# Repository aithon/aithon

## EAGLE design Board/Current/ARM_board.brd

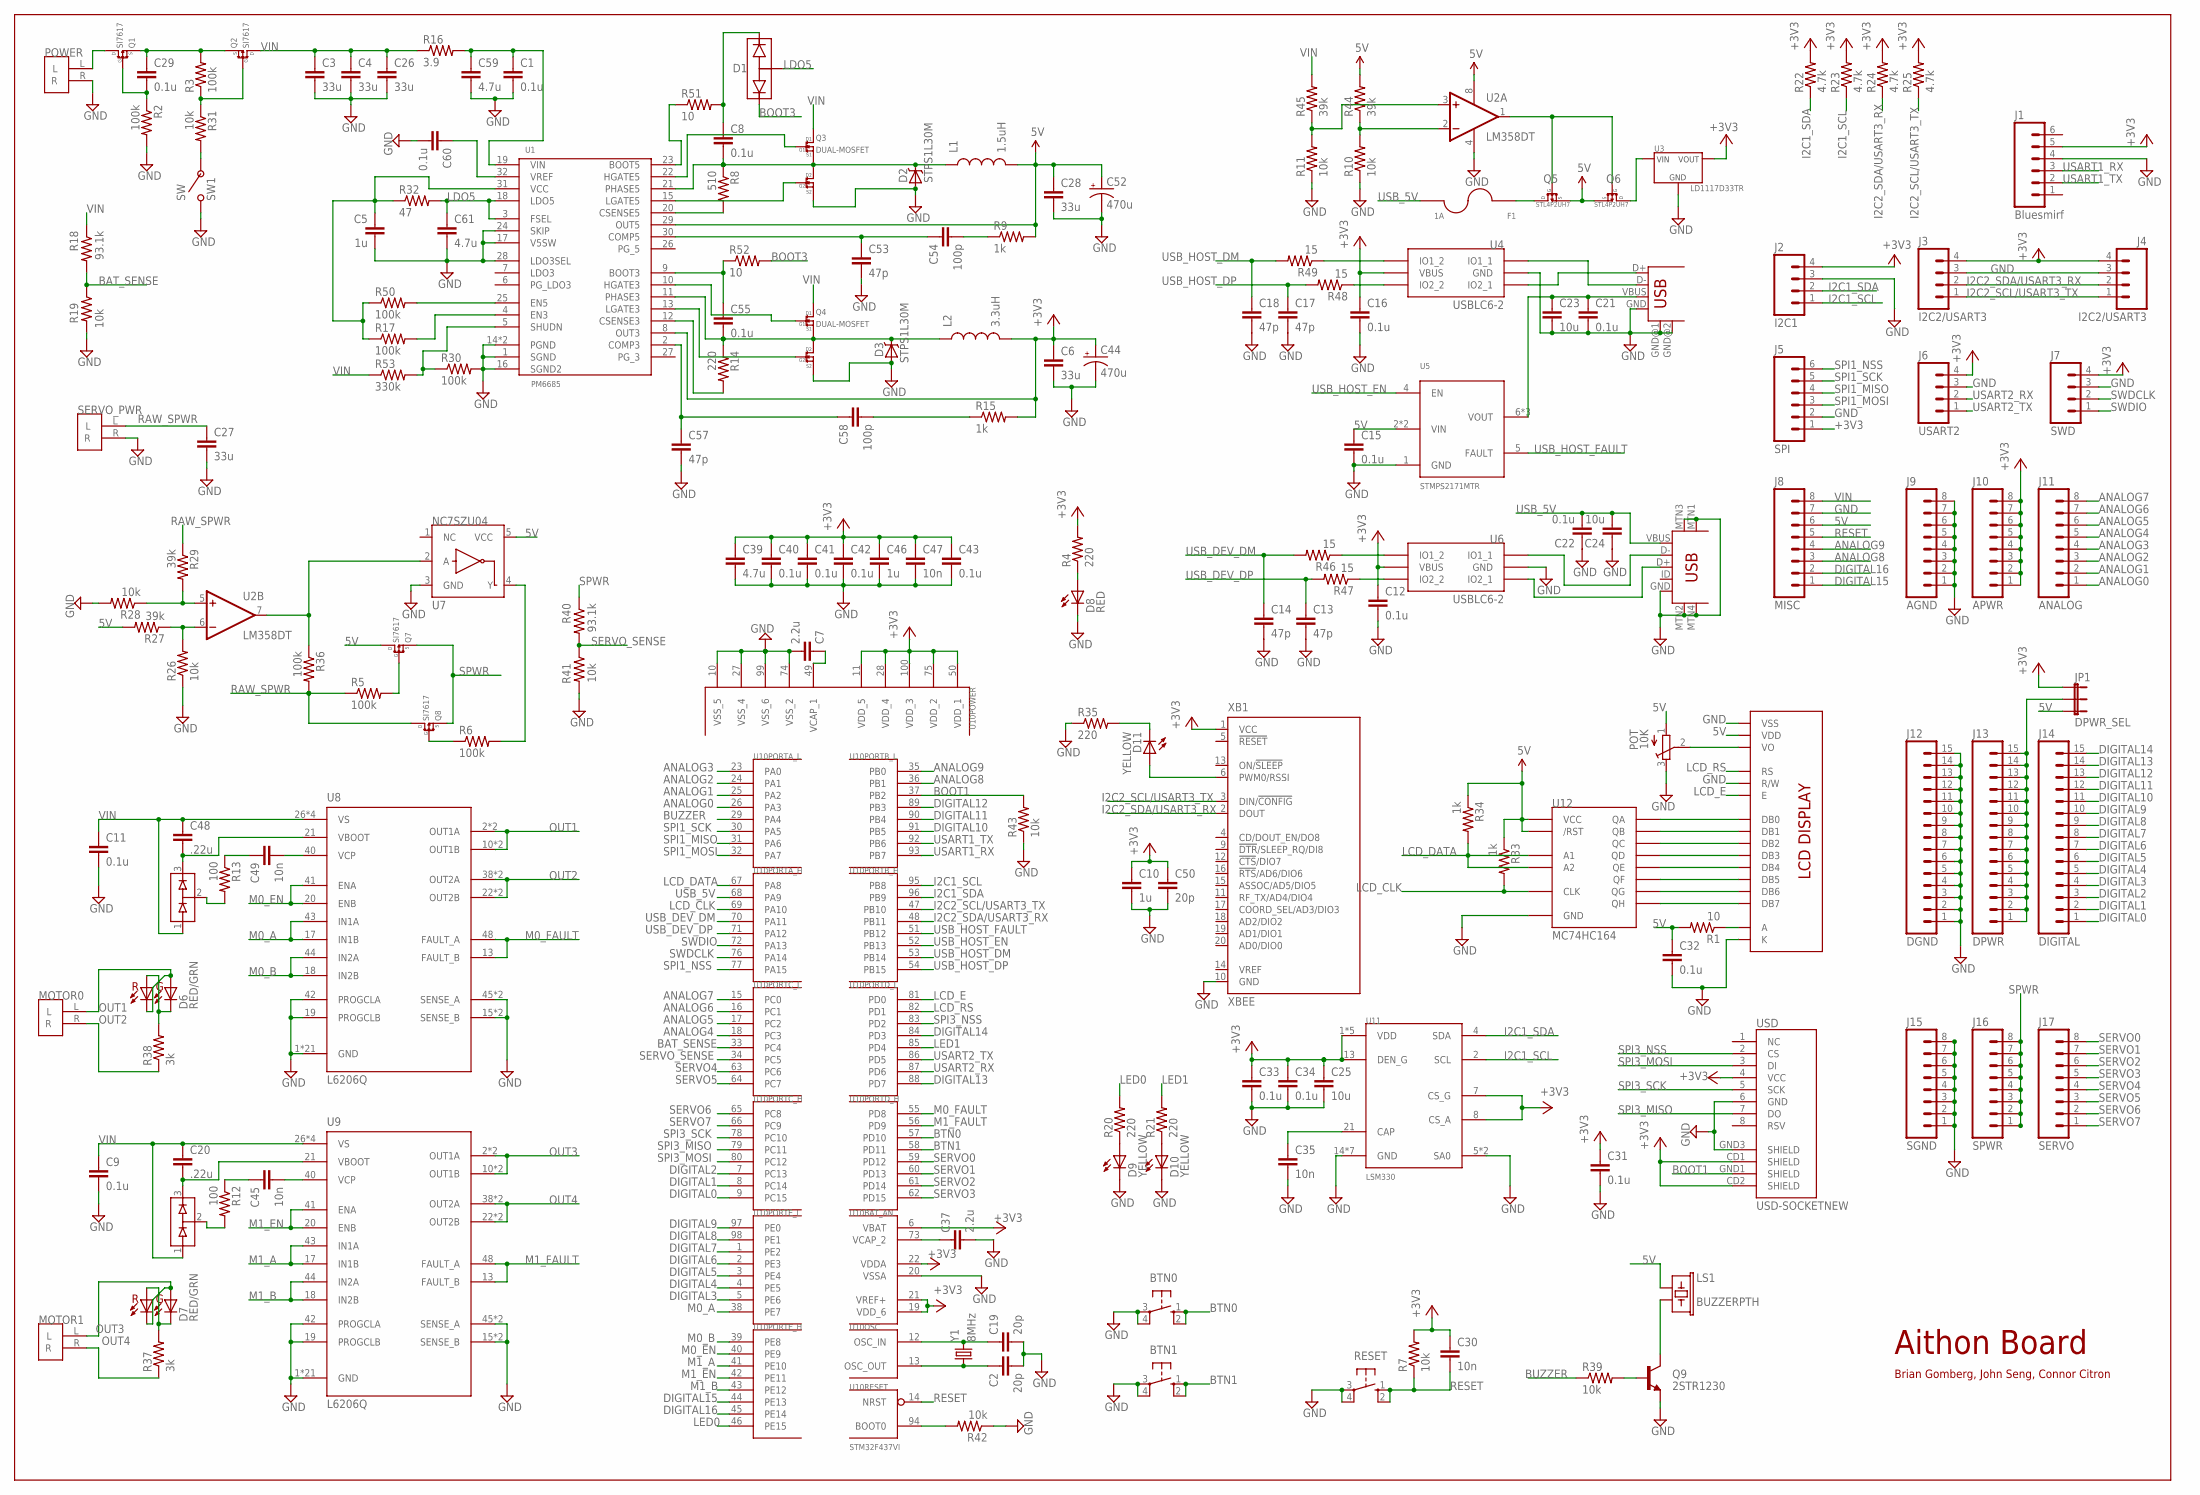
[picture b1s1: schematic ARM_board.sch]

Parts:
BTN0, BTN1: 10-XX; B3F-10XX
C1, C8, C9, C11, C12, C15, C16, C21, C22, C29, C31, C32, C33, C34, C40, C41, C42, C43, C55, C60: 0.1u; 0402-CAP
C2, C19, C50: 20p; 0402-CAP
C3, C4, C26, C27: 33u; 1206
C5, C10, C46: 1u; 0402-CAP
C6, C28: 33u; 0805
C7, C37: 2.2u; 0402-CAP
C13, C14, C17, C18, C53, C57: 47p; 0402-CAP
C20, C48: .22u; 0402-CAP
C23, C24, C25: 10u; 0603-CAP
C30, C35, C45, C47, C49: 10n; 0402-CAP
C39, C59, C61: 4.7u; 0603-CAP
C44, C52: 470u; PANASONIC_D
C54, C58: 100p; 0402-CAP
D1: BAS70-06FILM; SOT-23
D2, D3: STPS1L30M
D4: BAS70-05FILM; SOT-23
D5: BAV99; SOT-23
D6, D7: RED/GRN; LED-0606
D8: RED; CHIP-LED0603
D9, D10, D11: YELLOW; CHIP-LED0603
F1: 1A; 1206
J1: Bluesmirf; 1X06
J2: I2C1; 1X04
J3, J4: I2C2/USART3; 1X04
J5: SPI; 1X06
J6: USART2; 1X04
J7: SWD; 1X04
J8: MISC; 1X08
J9: AGND; 1X08
J10: APWR; 1X08
J11: ANALOG; 1X08
J12: DGND; 1X15
J13: DPWR; 1X15
J14: DIGITAL; 1X15
J15: SGND; 1X08
J16: SPWR; 1X08
J17: SERVO; 1X08
JP1: DPWR_SEL; 1X03
L1: 1.5uH; INDUCTOR-LMIP707
L2: 3.3uH; INDUCTOR-0520CDMCDS
LCD: LCD_DISPLAY; LCD
LS1: BUZZERPTH; BUZZER-12MM
MOTOR0, MOTOR1: 2POS_TERMINAL
POT: 10K; POT
POWER: 2POS_TERMINAL
Q1, Q2, Q7, Q8: SI7617; POWERPAK1212-8
Q3, Q4: DUAL-MOSFET; DUAL-MOSFET-STL60N32N3LL
Q5, Q6: STL4P2UH7; POWERFLAT
Q9: 2STR1230; SOT23-3
R1, R51, R52: 10; 0402-RES
R2, R3, R5, R6, R17, R30, R36, R50: 100k; 0402-RES
R4, R14, R20, R21, R35: 220; 0402-RES
R7, R10, R11, R19, R26, R28, R31, R39, R41, R42, R43: 10k; 0402-RES
R8: 510; 0402-RES
R9, R15, R33, R34: 1k; 0402-RES
R12, R13: 100; 0402-RES
R16: 3.9; 0402-RES
R18, R40: 93.1k; 0402-RES
R22, R23, R24, R25: 4.7k; 0402-RES
R27, R29, R44, R45: 39k; 0402-RES
R32: 47; 0402-RES
R37, R38: 3k; 0603-RES
R46, R47, R48, R49: 15; 0402-RES
R53: 330k; 0402-RES
RESET: 10-XX; B3F-10XX
SERVO_PWR: 2POS_TERMINAL
SW1: SW
U1: PM6685; VFQFPN-32
U2: LM358DT; SO08
U3: LD1117D33TR; 8-SOIC
U4, U6: USBLC6-2; SOT23-6L
U5: STMPS2171MTR; 8-SOIC
U7: NC7SZU04; SC70
U8, U9: L6206Q; VFQFPN48
U10: STM32F437VI; TQFP100
U11: LSM330
U12: MC74HC164; TSSOP-14
USB1: USB-A-S
USB2: USB-MINIB-5PIN; USB-MINIB
USD: USD-SOCKETNEW; MICRO-SD-SOCKET-PP
XB1: XBEE; MPN XBP24-Z7UIT-004
Y1: 8MHz; HC49UP

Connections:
5V: C15.1, C28.1, C32.1, C52.+, J8.6, JP1.3, L1.P$2 (2), LCD.VDD, LS1.+ (1), POT.1 (A), Q5.4 (S), Q5.7 (S), Q6.4 (S), Q6.7 (S), Q7.5 (D), Q7.6 (D), Q7.7 (D), Q7.8 (D), Q7.PAD (D), R1.2, R9.2, R27.2, R33.1, R34.1, R44.2, U1.29 (OUT5), U2.8 (V+), U5.2 (VIN), U5.3 (VIN), U7.5 (VCC), U12.9 (/RST), U12.14 (VCC)
+3V3: C6.1, C10.1, C12.1, C16.1, C25.1, C30.1, C31.1, C33.1, C34.1, C39.1, C40.1, C41.1, C42.1, C43.1, C44.+, C46.1, C47.1, C50.1, J1.5, J2.4, J3.4, J4.4, J5.1, J6.4, J7.4, J10.1, J10.2, J10.3, J10.4, J10.5, J10.6, J10.7, J10.8, JP1.1, L2.P$2 (2), R4.2, R7.2, R15.2, R22.2, R23.2, R24.2, R25.2, U1.8 (OUT3), U3.2 (VOUT), U3.3 (VOUT), U3.6 (VOUT), U3.7 (VOUT), U4.P$5 (VBUS), U6.P$5 (VBUS), U10.6 (VBAT), U10.11 (VDD_5), U10.19 (VDD_6), U10.21 (VREF+), U10.22 (VDDA), U10.28 (VDD_4), U10.50 (VDD_1), U10.75 (VDD_2), U10.100 (VDD_3), U11.1 (VDD), U11.3 (VDD), U11.7 (CS_G), U11.8 (CS_A), U11.13 (DEN_G), U11.22 (VDD), U11.23 (VDD), U11.24 (VDD), USD.4 (VCC), USD.CD1 (SHIELD), USD.CD2 (SHIELD), XB1.1 (VCC)
ANALOG0: J11.1, U10.26 (PA3)
ANALOG1: J11.2, U10.25 (PA2)
ANALOG2: J11.3, U10.24 (PA1)
ANALOG3: J11.4, U10.23 (PA0)
ANALOG4: J11.5, U10.18 (PC3)
ANALOG5: J11.6, U10.17 (PC2)
ANALOG6: J11.7, U10.16 (PC1)
ANALOG7: J11.8, U10.15 (PC0)
ANALOG8: J8.3, U10.36 (PB1)
ANALOG9: J8.4, U10.35 (PB0)
BAT_SENSE: R18.2, R19.1, U10.33 (PC4)
BOOT1: R43.2, U10.37 (PB2), USD.GND1 (SHIELD)
BOOT3: D1.P$2, R52.2
BTN0: BTN0.1 (S), BTN0.2 (S1), U10.57 (PD10)
BTN1: BTN1.1 (S), BTN1.2 (S1), U10.58 (PD11)
BUZZER: R39.1, U10.29 (PA4)
DIGITAL0: J14.1, U10.9 (PC15)
DIGITAL1: J14.2, U10.8 (PC14)
DIGITAL2: J14.3, U10.7 (PC13)
DIGITAL3: J14.4, U10.5 (PE6)
DIGITAL4: J14.5, U10.4 (PE5)
DIGITAL5: J14.6, U10.3 (PE4)
DIGITAL6: J14.7, U10.2 (PE3)
DIGITAL7: J14.8, U10.1 (PE2)
DIGITAL8: J14.9, U10.98 (PE1)
DIGITAL9: J14.10, U10.97 (PE0)
DIGITAL10: J14.11, U10.91 (PB5)
DIGITAL11: J14.12, U10.90 (PB4)
DIGITAL12: J14.13, U10.89 (PB3)
DIGITAL13: J14.14, U10.88 (PD7)
DIGITAL14: J14.15, U10.84 (PD3)
DIGITAL15: J8.1, U10.44 (PE13)
DIGITAL16: J8.2, U10.45 (PE14)
GND: BTN0.3, BTN0.4 (P1), BTN1.3, BTN1.4 (P1), C1.2, C2.2, C3.2, C4.2, C5.2, C6.2, C7.2, C9.2, C10.2, C11.2, C12.2, C13.2, C14.2, C15.2, C16.2, C17.2, C18.2, C19.2, C21.2, C22.1, C23.2, C24.1, C25.2, C26.2, C27.2, C28.2, C31.2, C32.2, C33.2, C34.2, C35.2, C37.2, C39.2, C40.2, C41.2, C42.2, C43.2, C44.-, C46.2, C47.2, C50.2, C52.-, C53.2, C57.2, C59.2, C60.2, C61.2, D2.P$1 (A), D3.P$1 (A), D8.C, D9.C, D10.C, J1.4, J2.3, J3.3, J4.3, J5.2, J6.3, J7.3, J8.7, J9.1, J9.2, J9.3, J9.4, J9.5, J9.6, J9.7, J9.8, J12.1, J12.2, J12.3, J12.4, J12.5, J12.6, J12.7, J12.8, J12.9, J12.10, J12.11, J12.12, J12.13, J12.14, J12.15, J15.1, J15.2, J15.3, J15.4, J15.5, J15.6, J15.7, J15.8, LCD.K, LCD.R/W, LCD.VSS, POT.3 (E), POWER.R, Q3.5/6/7 (S2), Q4.5/6/7 (S2), Q9.2 (E), R2.2, R10.1, R11.1, R19.2, R26.1, R28.2, R30.2, R35.1, R41.2, R42.1, R43.1, RESET.3, RESET.4 (P1), SERVO_PWR.R, SW1.P$1, SW1.P$3, U1.1 (SGND), U1.14 (PGND), U1.16 (SGND2), U1.17 (V5SW), U1.24 (SKIP), U1.28 (LDO3SEL), U1.PAD (PGND), U2.4 (V-), U3.1 (GND), U4.P$2 (GND), U5.1 (GND), U6.P$2 (GND), U7.3 (GND), U8.1 (GND), U8.4 (GND), U8.5 (GND), U8.6 (GND), U8.7 (GND), U8.8 (GND), U8.9 (GND), U8.12 (GND), U8.14 (GND), U8.15 (SENSE_B), U8.16 (SENSE_B)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
I2C1_SCL: J2.1, R23.1, U10.95 (PB8), U11.2 (SCL)
I2C1_SDA: J2.2, R22.1, U10.96 (PB9), U11.4 (SDA)
I2C2_SCL/USART3_TX: J3.1, J4.1, R25.1, U10.47 (PB10), XB1.3 (DIN/!CONFIG)
I2C2_SDA/USART3_RX: J3.2, J4.2, R24.1, U10.48 (PB11), XB1.2 (DOUT)
LCD_CLK: R33.2, U10.69 (PA10), U12.8 (CLK)
LCD_DATA: R34.2, U10.67 (PA8), U12.1 (A1), U12.2 (A2)
LCD_E: LCD.E, U10.81 (PD0)
LCD_RS: LCD.RS, U10.82 (PD1)
LDO5: C61.1, D1.P$0, R32.2, U1.3 (FSEL), U1.18 (LDO5)
LED0: R20.2, U10.46 (PE15)
LED1: R21.2, U10.85 (PD4)
M0_A: U8.17 (IN1B), U8.43 (IN1A), U10.38 (PE7)
M0_B: U8.18 (IN2B), U8.44 (IN2A), U10.39 (PE8)
M0_EN: U8.20 (ENB), U8.41 (ENA), U10.40 (PE9)
M0_FAULT: U8.13 (FAULT_B), U8.48 (FAULT_A), U10.55 (PD8)
M1_A: U9.17 (IN1B), U9.43 (IN1A), U10.41 (PE10)
M1_B: U9.18 (IN2B), U9.44 (IN2A), U10.43 (PE12)
M1_EN: U9.20 (ENB), U9.41 (ENA), U10.42 (PE11)
M1_FAULT: U9.13 (FAULT_B), U9.48 (FAULT_A), U10.56 (PD9)
unnamed: POWER.L, Q1.5 (D), Q1.6 (D), Q1.7 (D), Q1.8 (D), Q1.PAD (D)
unnamed: C29.2, Q1.4 (G), R2.1
unnamed: R42.2, U10.94 (BOOT0)
unnamed: C37.1, U10.73 (VCAP_2)
unnamed: R11.2, R45.1, U2.3 (+IN)
unnamed: R46.1, U6.P$6 (IO1_2)
unnamed: C60.1, U1.32 (VREF)
unnamed: U6.P$3 (IO2_1), USB2.D+
unnamed: D8.A, R4.1
unnamed: R31.2, SW1.P$2
unnamed: C35.1, U11.21 (CAP)
unnamed: R28.1, R29.2, U2.5 (+IN)
unnamed: U4.P$3 (IO2_1), USB1.D+
unnamed: Q5.3 (G), Q6.3 (G), U2.1 (OUT)
unnamed: C5.1, R17.1, R32.1, R50.1, U1.31 (VCC)
unnamed: U4.P$1 (IO1_1), USB1.D-
unnamed: U6.P$1 (IO1_1), USB2.D-
unnamed: D11.C, R35.2
unnamed: J13.1, J13.2, J13.3, J13.4, J13.5, J13.6, J13.7, J13.8, J13.9, J13.10, J13.11, J13.12, J13.13, J13.14, J13.15, JP1.2
unnamed: R51.1, U1.23 (BOOT5)
unnamed: C21.1, C23.1, U5.6 (VOUT), U5.7 (VOUT), U5.8 (VOUT), USB1.VBUS
unnamed: Q6.1 (D), Q6.2 (D), Q6.5 (D), Q6.6 (D), Q6.8 (D), U3.4 (VIN)
unnamed: C29.1, Q1.1 (S), Q1.2 (S), Q1.3 (S), Q2.1 (S), Q2.2 (S), Q2.3 (S), R3.2
unnamed: C7.1, U10.49 (VCAP_1)
unnamed: C8.1, D1.P$1, R51.2
unnamed: R26.2, R27.1, U2.6 (-IN)
unnamed: R36.1, U2.7 (OUT), U7.2 (A)
unnamed: LS1.- (2), Q9.3 (C)
unnamed: D11.A, XB1.6 (PWM0/RSSI)
unnamed: R6.2, U7.4 (Y)
unnamed: LCD.VO, POT.2 (S)
unnamed: F1.1, Q5.1 (D), Q5.2 (D), Q5.5 (D), Q5.6 (D), Q5.8 (D)
unnamed: R47.1, U6.P$4 (IO2_2)
unnamed: R48.1, U4.P$4 (IO2_2)
unnamed: R10.2, R44.1, U2.2 (-IN)
unnamed: R49.1, U4.P$6 (IO1_2)
unnamed: C45.1, R12.1
unnamed: C45.2, U9.40 (VCP)
unnamed: C20.2, D5.3, U9.21 (VBOOT)
unnamed: D5.2, R12.2
unnamed: C49.1, R13.1
unnamed: D9.A, R20.1
unnamed: D10.A, R21.1
unnamed: Q4.8 (G2), U1.13 (LGATE3)
unnamed: C49.2, U8.40 (VCP)
unnamed: C19.1, U10.12 (OSC_IN), Y1.2
unnamed: C2.1, U10.13 (OSC_OUT), Y1.1
unnamed: C48.2, D4.3, U8.21 (VBOOT)
unnamed: D4.2, R13.2
unnamed: Q7.4 (G), R5.2
unnamed: D7.1, D7.4, R37.2
unnamed: D6.1, D6.4, R38.2
unnamed: Q8.4 (G), R6.1
unnamed: LCD.A, R1.1
unnamed: R8.2, U1.20 (CSENSE5)
unnamed: Q3.1 (G1), U1.22 (HGATE5)
unnamed: Q3.8 (G2), U1.15 (LGATE5)
unnamed: LCD.DB0, U12.3 (QA)
unnamed: C55.1, R52.1, U1.9 (BOOT3)
unnamed: LCD.DB1, U12.4 (QB)
unnamed: LCD.DB2, U12.5 (QC)
unnamed: LCD.DB3, U12.6 (QD)
unnamed: LCD.DB4, U12.10 (QE)
unnamed: LCD.DB5, U12.11 (QF)
unnamed: Q9.1 (B), R39.2
unnamed: C8.2, D2.C2 (C), D2.P$2 (C), L1.P$1 (1), Q3.S1D2 (S1), R8.1, U1.21 (PHASE5)
unnamed: C54.2, R9.1
unnamed: Q2.4 (G), R3.1, R31.1
unnamed: C53.1, C54.1, U1.30 (COMP5)
unnamed: LCD.DB6, U12.12 (QG)
unnamed: LCD.DB7, U12.13 (QH)
unnamed: Q4.1 (G1), U1.10 (HGATE3)
unnamed: C55.2, D3.C2 (C), D3.P$2 (C), L2.P$1 (1), Q4.S1D2 (S1), R14.1, U1.11 (PHASE3)
unnamed: R14.2, U1.12 (CSENSE3)
unnamed: C57.1, C58.1, U1.2 (COMP3)
unnamed: C58.2, R15.1
unnamed: C1.1, C59.1, R16.2, U1.19 (VIN)
unnamed: R30.1, R53.2, U1.5 (SHUDN)
unnamed: R17.2, U1.4 (EN3)
unnamed: R50.2, U1.25 (EN5)
OUT1: D6.2, D6.3, MOTOR0.L, U8.2 (OUT1A), U8.3 (OUT1A), U8.10 (OUT1B), U8.11 (OUT1B)
OUT2: MOTOR0.R, R38.1, U8.22 (OUT2B), U8.23 (OUT2B), U8.38 (OUT2A), U8.39 (OUT2A)
OUT3: D7.2, D7.3, MOTOR1.L, U9.2 (OUT1A), U9.3 (OUT1A), U9.10 (OUT1B), U9.11 (OUT1B)
OUT4: MOTOR1.R, R37.1, U9.22 (OUT2B), U9.23 (OUT2B), U9.38 (OUT2A), U9.39 (OUT2A)
RAW_SPWR: C27.1, Q8.5 (D), Q8.6 (D), Q8.7 (D), Q8.8 (D), Q8.PAD (D), R5.1, R29.1, R36.2, SERVO_PWR.L
RESET: C30.2, J8.5, R7.1, RESET.1 (S), RESET.2 (S1), U10.14 (NRST)
SERVO0: J17.8, U10.59 (PD12)
SERVO1: J17.7, U10.60 (PD13)
SERVO2: J17.6, U10.61 (PD14)
SERVO3: J17.5, U10.62 (PD15)
SERVO4: J17.4, U10.63 (PC6)
SERVO5: J17.3, U10.64 (PC7)
SERVO6: J17.2, U10.65 (PC8)
SERVO7: J17.1, U10.66 (PC9)
SERVO_SENSE: R40.2, R41.1, U10.34 (PC5)
SPI1_MISO: J5.4, U10.31 (PA6)
SPI1_MOSI: J5.3, U10.32 (PA7)
SPI1_NSS: J5.6, U10.77 (PA15)
SPI1_SCK: J5.5, U10.30 (PA5)
SPI3_MISO: U10.79 (PC11), USD.7 (DO)
SPI3_MOSI: U10.80 (PC12), USD.3 (DI)
SPI3_NSS: U10.83 (PD2), USD.2 (CS)
SPI3_SCK: U10.78 (PC10), USD.5 (SCK)
SPWR: J16.1, J16.2, J16.3, J16.4, J16.5, J16.6, J16.7, J16.8, Q7.1 (S), Q7.2 (S), Q7.3 (S), Q8.1 (S), Q8.2 (S), Q8.3 (S), R40.1
SWDCLK: J7.2, U10.76 (PA14)
SWDIO: J7.1, U10.72 (PA13)
USART1_RX: J1.3, U10.93 (PB7)
USART1_TX: J1.2, U10.92 (PB6)
USART2_RX: J6.2, U10.87 (PD6)
USART2_TX: J6.1, U10.86 (PD5)
USB_5V: C22.2, C24.2, F1.2, U10.68 (PA9), USB2.VBUS
USB_DEV_DM: C14.1, R46.2, U10.70 (PA11)
USB_DEV_DP: C13.1, R47.2, U10.71 (PA12)
USB_HOST_DM: C18.1, R49.2, U10.53 (PB14)
USB_HOST_DP: C17.1, R48.2, U10.54 (PB15)
USB_HOST_EN: U5.4 (EN), U10.52 (PB13)
USB_HOST_FAULT: U5.5 (FAULT), U10.51 (PB12)
VIN: C3.1, C4.1, C9.1, C11.1, C20.1, C26.1, C48.1, D4.1, D5.1, J8.8, Q2.5 (D), Q2.6 (D), Q2.7 (D), Q2.8 (D), Q2.PAD (D), Q3.2/3/4 (D1), Q3.D1, Q4.2/3/4 (D1), Q4.D1, R16.1, R18.1, R45.2, R53.1, U8.26 (VS), U8.27 (VS), U8.34 (VS), U8.35 (VS), U9.26 (VS), U9.27 (VS), U9.34 (VS), U9.35 (VS)

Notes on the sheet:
Aithon Board
Brian Gomberg, John Seng, Connor Citron

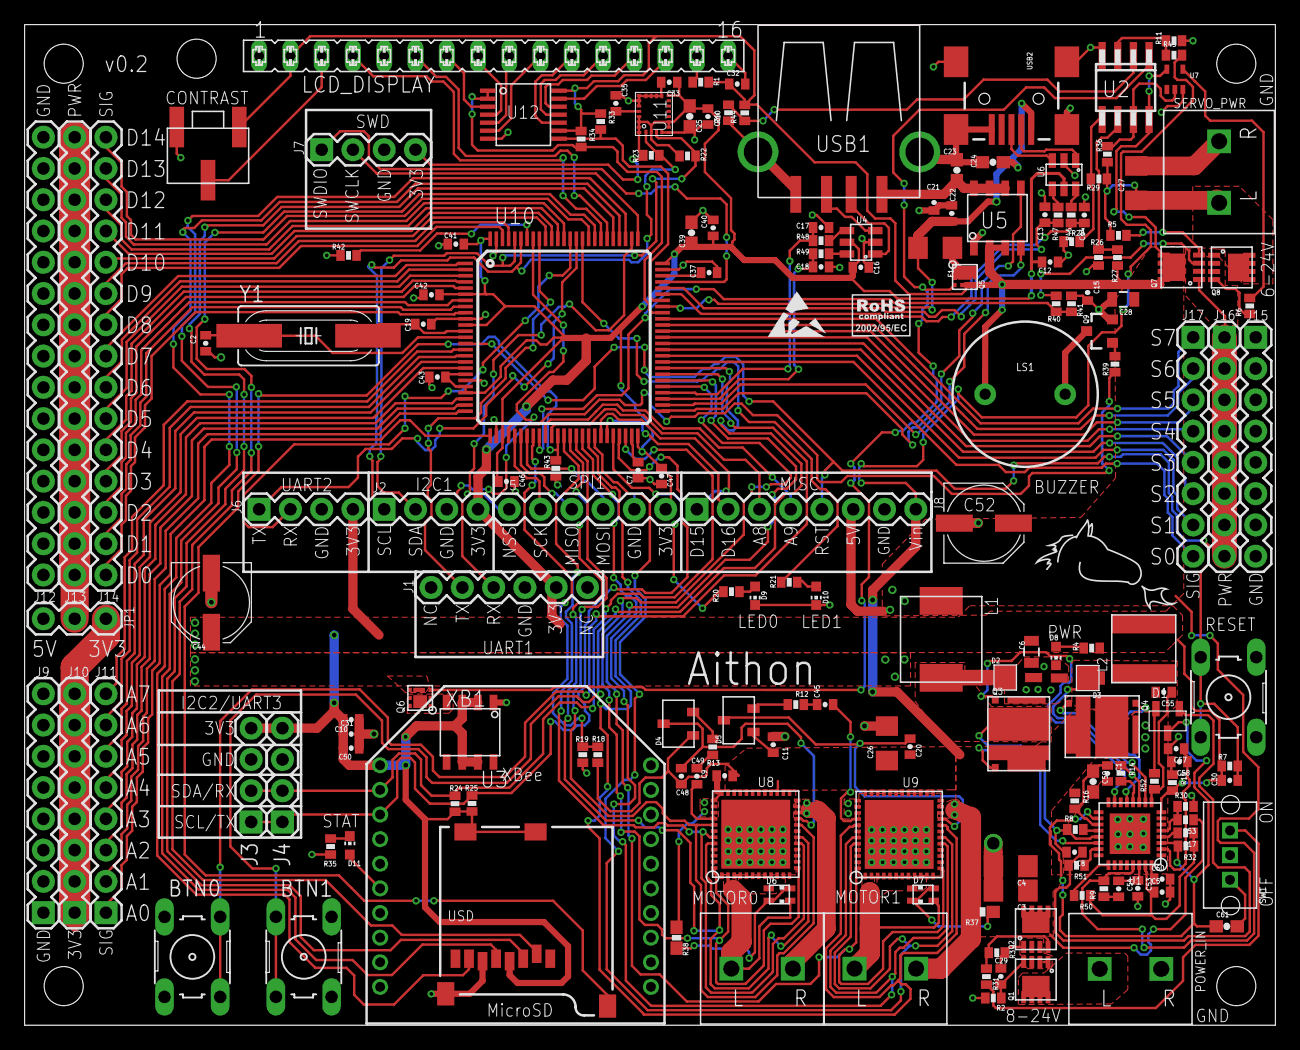
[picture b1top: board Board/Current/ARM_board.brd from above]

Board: 2 copper layers, 101.6 x 81.3 mm, 179 parts (0 on the bottom side), 173 nets.

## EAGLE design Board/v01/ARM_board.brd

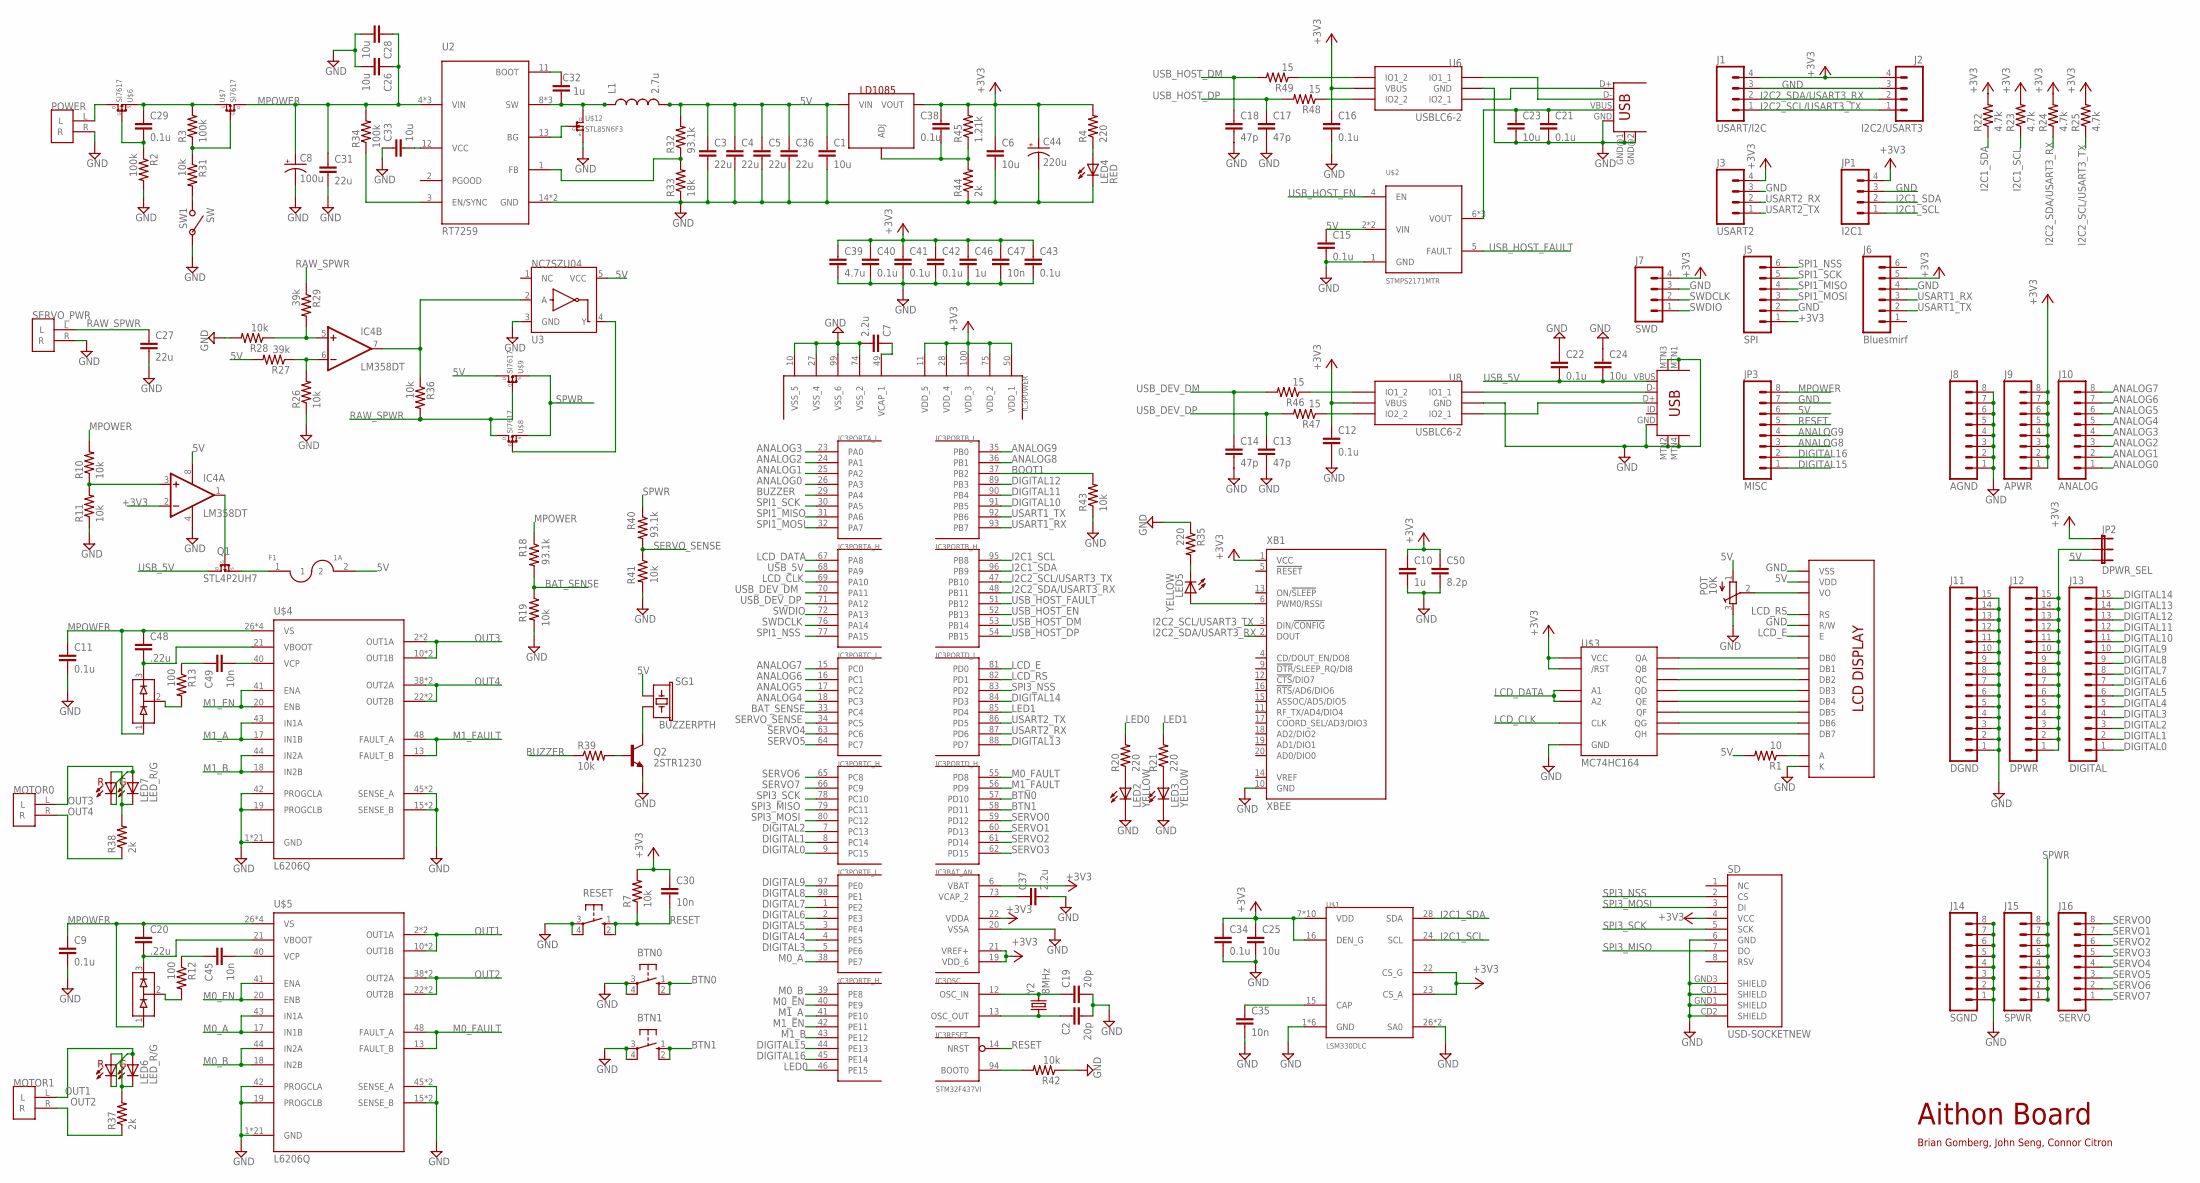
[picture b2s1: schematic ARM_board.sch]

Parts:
BTN0, BTN1: 10-XX; B3F-10XX
C1, C6, C25, C33: 10u; 0603-CAP
C2, C19: 20p; 0402-CAP
C3, C4, C5, C36: 22u; 0805
C7, C37: 2.2u; 0402-CAP
C8: 100u; PANASONIC_D
C9: 0.1u; 0603-CAP
C10, C32: 1u; 0603-CAP
C11: 0.1u; 0805
C12, C15, C16, C21, C22, C29, C34, C38, C40, C41, C42, C43: 0.1u; 0402-CAP
C13, C14, C17, C18: 47p; 0402-CAP
C20, C48: .22u; 0402-CAP
C23, C24, C26, C28: 10u; 0805
C27, C31: 22u; 1206
C30, C35, C45, C47, C49: 10n; 0402-CAP
C39: 4.7u; 0603-CAP
C44: 220u; PANASONIC_D
C46: 1u; 0402-CAP
C50: 8.2p; 0402-CAP
F1: 1A; 1206
IC3: STM32F437VI; TQFP100
IC4: LM358DT; SO08
J1: USART/I2C; 1X04
J2: I2C2/USART3; 1X04
J3: USART2; 1X04
J5: SPI; 1X06
J6: Bluesmirf; 1X06
J7: SWD; 1X04
J8: AGND; 1X08
J9: APWR; 1X08
J10: ANALOG; 1X08
J11: DGND; 1X15
J12: DPWR; 1X15
J13: DIGITAL; 1X15
J14: SGND; 1X08
J15: SPWR; 1X08
J16: SERVO; 1X08
JP1: I2C1; 1X04
JP2: DPWR_SEL; 1X03
JP3: MISC; 1X08
L1: 2.7u; INDUCTOR
LCD: LCD_DISPLAY; LCD
LD1085: AP1084; DPAK
LED2, LED3, LED5: YELLOW; CHIP-LED0603
LED4: RED; CHIP-LED0603
LED6, LED7: LED_R/G; LED-0606
MOTOR0, MOTOR1: 2POS_TERMINAL
POT: 10K; POT
POWER: 2POS_TERMINAL
Q1: STL4P2UH7; POWERFLAT
Q2: 2STR1230; SOT23-3
R1: 10; 0402-RES
R2, R3, R34: 100k; 0402-RES
R4, R20, R21, R35: 220; 0402-RES
R7, R10, R11, R19, R26, R28, R31, R36, R39, R41, R42, R43: 10k; 0402-RES
R12, R13: 100; 0402-RES
R18, R32, R40: 93.1k; 0402-RES
R22, R23, R24, R25: 4.7k; 0402-RES
R27, R29: 39k; 0402-RES
R33: 18k; 0402-RES
R37, R38, R44: 2k; 0402-RES
R45: 1.21k; 0402-RES
R46, R47, R48, R49: 15; 0402-RES
RESET: 10-XX; B3F-10XX
SD: USD-SOCKETNEW; MICRO-SD-SOCKET-PP
SERVO_PWR: 2POS_TERMINAL
SG1: BUZZERPTH; BUZZER-12MM
SW1: SW
U2: RT7259; WDFN-14L
U3: NC7SZU04; SC70
U6, U8: USBLC6-2; SOT23-6L
U$1: LSM330DLC; LGA-28
U$2: STMPS2171MTR; 8-SOIC
U$3: MC74HC164; TSSOP-14
U$4, U$5: L6206Q; VFQFPN48
U$6, U$7, U$8, U$9: SI7617; POWERPAK1212-8
U$10, U$11: BAV99; SOT-23
U$12: STL85N6F3; POWERFLAT5X6
USB1: USB-A-S
USB2: USB-MINIB-5PIN; USB-MINIB
XB1: XBEE; MPN XBP24-Z7UIT-004
Y2: 8MHz; HC49UP

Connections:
5V: C1.1, C3.1, C4.1, C5.1, C15.1, C36.1, F1.2, IC4.8 (V+), JP2.3, JP3.6, L1.P$2 (2), LCD.VDD, LD1085.3 (VIN), POT.1 (A), R1.2, R27.2, R32.2, SG1.+ (1), U3.5 (VCC), U$2.2 (VIN), U$2.3 (VIN), U$9.5 (D), U$9.6 (D), U$9.7 (D), U$9.8 (D), U$9.PAD (D)
+3V3: C6.1, C10.1, C12.1, C16.1, C25.1, C30.1, C34.1, C38.1, C39.1, C40.1, C41.1, C42.1, C43.1, C44.+, C46.1, C47.1, C50.1, IC3.6 (VBAT), IC3.11 (VDD_5), IC3.19 (VDD_6), IC3.21 (VREF+), IC3.22 (VDDA), IC3.28 (VDD_4), IC3.50 (VDD_1), IC3.75 (VDD_2), IC3.100 (VDD_3), IC4.2 (-IN), J1.4, J2.4, J3.4, J5.1, J6.5, J7.4, J9.1, J9.2, J9.3, J9.4, J9.5, J9.6, J9.7, J9.8, JP1.4, JP2.1, LD1085.TAB (VOUT), R4.2, R7.2, R22.2, R23.2, R24.2, R25.2, R45.2, SD.4 (VCC), U6.P$5 (VBUS), U8.P$5 (VBUS), U$1.7 (VDD), U$1.8 (VDD), U$1.9 (VDD), U$1.10 (VDD), U$1.11 (VDD), U$1.12 (VDD), U$1.13 (VDD), U$1.14 (VDD), U$1.16 (DEN_G), U$1.21 (VDD), U$1.22 (CS_G), U$1.23 (CS_A), U$1.25 (VDD), U$3.9 (/RST), U$3.14 (VCC), XB1.1 (VCC)
ANALOG0: IC3.26 (PA3), J10.1
ANALOG1: IC3.25 (PA2), J10.2
ANALOG2: IC3.24 (PA1), J10.3
ANALOG3: IC3.23 (PA0), J10.4
ANALOG4: IC3.18 (PC3), J10.5
ANALOG5: IC3.17 (PC2), J10.6
ANALOG6: IC3.16 (PC1), J10.7
ANALOG7: IC3.15 (PC0), J10.8
ANALOG8: IC3.36 (PB1), JP3.3
ANALOG9: IC3.35 (PB0), JP3.4
BAT_SENSE: IC3.33 (PC4), R18.2, R19.1
BOOT1: IC3.37 (PB2), R43.2
BTN0: BTN0.1 (S), BTN0.2 (S1), IC3.57 (PD10)
BTN1: BTN1.1 (S), BTN1.2 (S1), IC3.58 (PD11)
BUZZER: IC3.29 (PA4), R39.1
DIGITAL0: IC3.9 (PC15), J13.1
DIGITAL1: IC3.8 (PC14), J13.2
DIGITAL2: IC3.7 (PC13), J13.3
DIGITAL3: IC3.5 (PE6), J13.4
DIGITAL4: IC3.4 (PE5), J13.5
DIGITAL5: IC3.3 (PE4), J13.6
DIGITAL6: IC3.2 (PE3), J13.7
DIGITAL7: IC3.1 (PE2), J13.8
DIGITAL8: IC3.98 (PE1), J13.9
DIGITAL9: IC3.97 (PE0), J13.10
DIGITAL10: IC3.91 (PB5), J13.11
DIGITAL11: IC3.90 (PB4), J13.12
DIGITAL12: IC3.89 (PB3), J13.13
DIGITAL13: IC3.88 (PD7), J13.14
DIGITAL14: IC3.84 (PD3), J13.15
DIGITAL15: IC3.44 (PE13), JP3.1
DIGITAL16: IC3.45 (PE14), JP3.2
GND: BTN0.3, BTN0.4 (P1), BTN1.3, BTN1.4 (P1), C1.2, C2.2, C3.2, C4.2, C5.2, C6.2, C7.2, C8.-, C9.2, C10.2, C11.2, C12.2, C13.2, C14.2, C15.2, C16.2, C17.2, C18.2, C19.2, C21.2, C22.1, C23.2, C24.1, C25.2, C26.2, C27.2, C28.2, C31.2, C33.1, C34.2, C35.2, C36.2, C37.2, C39.2, C40.2, C41.2, C42.2, C43.2, C44.-, C46.2, C47.2, C50.2, IC3.10 (VSS_5), IC3.20 (VSSA), IC3.27 (VSS_4), IC3.74 (VSS_2), IC3.99 (VSS_6), IC4.4 (V-), J1.3, J2.3, J3.3, J5.2, J6.4, J7.3, J8.1, J8.2, J8.3, J8.4, J8.5, J8.6, J8.7, J8.8, J11.1, J11.2, J11.3, J11.4, J11.5, J11.6, J11.7, J11.8, J11.9, J11.10, J11.11, J11.12, J11.13, J11.14, J11.15, J14.1, J14.2, J14.3, J14.4, J14.5, J14.6, J14.7, J14.8, JP1.3, JP3.7, LCD.K, LCD.R/W, LCD.VSS, LED2.C, LED3.C, LED4.C, POT.3 (E), POWER.R, Q2.2 (E), R2.2, R11.1, R19.2, R26.1, R28.2, R33.1, R35.1, R41.2, R42.1, R43.1, R44.1, RESET.3, RESET.4 (P1), SD.6 (GND), SD.CD1 (SHIELD), SD.CD2 (SHIELD), SD.GND1 (SHIELD), SD.GND3 (SHIELD), SERVO_PWR.R, SW1.P$2, U2.14 (GND), U2.P$1 (GND), U3.3 (GND), U6.P$2 (GND), U8.P$2 (GND), U$1.1 (GND), U$1.2 (GND), U$1.3 (GND), U$1.4 (GND), U$1.5 (GND), U$1.6 (GND), U$1.26 (SA0), U$1.27 (SA0), U$2.1 (GND), U$3.7 (GND), U$4.1 (GND), U$4.4 (GND), U$4.5 (GND), U$4.6 (GND), U$4.7 (GND), U$4.8 (GND), U$4.9 (GND), U$4.12 (GND)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
I2C1_SCL: IC3.95 (PB8), JP1.1, R23.1, U$1.24 (SCL)
I2C1_SDA: IC3.96 (PB9), JP1.2, R22.1, U$1.28 (SDA)
I2C2_SCL/USART3_TX: IC3.47 (PB10), J1.1, J2.1, R25.1, XB1.3 (DIN/!CONFIG)
I2C2_SDA/USART3_RX: IC3.48 (PB11), J1.2, J2.2, R24.1, XB1.2 (DOUT)
LCD_CLK: IC3.69 (PA10), U$3.8 (CLK)
LCD_DATA: IC3.67 (PA8), U$3.1 (A1), U$3.2 (A2)
LCD_E: IC3.81 (PD0), LCD.E
LCD_RS: IC3.82 (PD1), LCD.RS
LED0: IC3.46 (PE15), R20.2
LED1: IC3.85 (PD4), R21.2
M0_A: IC3.38 (PE7), U$5.17 (IN1B), U$5.43 (IN1A)
M0_B: IC3.39 (PE8), U$5.18 (IN2B), U$5.44 (IN2A)
M0_EN: IC3.40 (PE9), U$5.20 (ENB), U$5.41 (ENA)
M0_FAULT: IC3.55 (PD8), U$5.13 (FAULT_B), U$5.48 (FAULT_A)
M1_A: IC3.41 (PE10), U$4.17 (IN1B), U$4.43 (IN1A)
M1_B: IC3.43 (PE12), U$4.18 (IN2B), U$4.44 (IN2A)
M1_EN: IC3.42 (PE11), U$4.20 (ENB), U$4.41 (ENA)
M1_FAULT: IC3.56 (PD9), U$4.13 (FAULT_B), U$4.48 (FAULT_A)
MPOWER: C8.+, C9.1, C11.1, C20.1, C26.1, C28.1, C31.1, C48.1, JP3.8, R10.2, R18.1, R34.2, U2.4 (VIN), U2.5 (VIN), U2.6 (VIN), U$4.26 (VS), U$4.27 (VS), U$4.34 (VS), U$4.35 (VS), U$5.26 (VS), U$5.27 (VS), U$5.34 (VS), U$5.35 (VS), U$7.5 (D), U$7.6 (D), U$7.7 (D), U$7.8 (D), U$7.PAD (D), U$10.1, U$11.1
unnamed: POWER.L, U$6.5 (D), U$6.6 (D), U$6.7 (D), U$6.8 (D), U$6.PAD (D)
unnamed: C29.2, R2.1, U$6.4 (G)
unnamed: IC3.94 (BOOT0), R42.2
unnamed: C37.1, IC3.73 (VCAP_2)
unnamed: IC4.3 (+IN), R10.1, R11.2
unnamed: R46.1, U8.P$6 (IO1_2)
unnamed: U8.P$1 (IO1_1), USB2.D-
unnamed: U8.P$3 (IO2_1), USB2.D+
unnamed: LED4.A, R4.1
unnamed: C32.2, L1.P$1 (1), U2.8 (SW), U2.9 (SW), U2.10 (SW), U$12.5 (D)
unnamed: C35.1, U$1.15 (CAP)
unnamed: IC4.5 (+IN), R28.1, R29.2
unnamed: U6.P$3 (IO2_1), USB1.D+
unnamed: IC4.1 (OUT), Q1.3 (G)
unnamed: F1.1, Q1.4 (S), Q1.7 (S)
unnamed: U6.P$1 (IO1_1), USB1.D-
unnamed: R32.1, R33.2, U2.1 (FB)
unnamed: LED5.C, R35.2
unnamed: J12.1, J12.2, J12.3, J12.4, J12.5, J12.6, J12.7, J12.8, J12.9, J12.10, J12.11, J12.12, J12.13, J12.14, J12.15, JP2.2
unnamed: C33.2, U2.12 (VCC)
unnamed: C21.1, C23.1, U$2.6 (VOUT), U$2.7 (VOUT), U$2.8 (VOUT), USB1.VBUS
unnamed: R31.2, SW1.P$1
unnamed: C29.1, R3.2, U$6.1 (S), U$6.2 (S), U$6.3 (S), U$7.1 (S), U$7.2 (S), U$7.3 (S)
unnamed: C7.1, IC3.49 (VCAP_1)
unnamed: C32.1, U2.11 (BOOT)
unnamed: IC4.6 (-IN), R26.2, R27.1
unnamed: IC4.7 (OUT), R36.1, U3.2 (A)
unnamed: Q2.3 (C), SG1.- (2)
unnamed: LED5.A, XB1.6 (PWM0/RSSI)
unnamed: U3.4 (Y), U$8.4 (G)
unnamed: LCD.VO, POT.2 (S)
unnamed: C38.2, LD1085.1 (ADJ), R44.2, R45.1
unnamed: R47.1, U8.P$4 (IO2_2)
unnamed: R48.1, U6.P$4 (IO2_2)
unnamed: U2.13 (BG), U$12.4 (G)
unnamed: R49.1, U6.P$6 (IO1_2)
unnamed: C45.1, R12.1
unnamed: C45.2, U$5.40 (VCP)
unnamed: C20.2, U$5.21 (VBOOT), U$10.3
unnamed: R12.2, U$10.2
unnamed: C49.1, R13.1
unnamed: LED2.A, R20.1
unnamed: LED3.A, R21.1
unnamed: R34.1, U2.3 (EN/SYNC)
unnamed: C49.2, U$4.40 (VCP)
unnamed: C19.1, IC3.12 (OSC_IN), Y2.2
unnamed: C2.1, IC3.13 (OSC_OUT), Y2.1
unnamed: C48.2, U$4.21 (VBOOT), U$11.3
unnamed: R13.2, U$11.2
unnamed: LED6.1, LED6.4, R37.2
unnamed: LED7.1, LED7.4, R38.2
unnamed: LCD.A, R1.1
unnamed: LCD.DB0, U$3.3 (QA)
unnamed: LCD.DB1, U$3.4 (QB)
unnamed: LCD.DB2, U$3.5 (QC)
unnamed: LCD.DB3, U$3.6 (QD)
unnamed: LCD.DB4, U$3.10 (QE)
unnamed: LCD.DB5, U$3.11 (QF)
unnamed: Q2.1 (B), R39.2
unnamed: R3.1, R31.1, U$7.4 (G)
unnamed: LCD.DB6, U$3.12 (QG)
unnamed: LCD.DB7, U$3.13 (QH)
OUT1: LED6.2, LED6.3, MOTOR1.L, U$5.2 (OUT1A), U$5.3 (OUT1A), U$5.10 (OUT1B), U$5.11 (OUT1B)
OUT2: MOTOR1.R, R37.1, U$5.22 (OUT2B), U$5.23 (OUT2B), U$5.38 (OUT2A), U$5.39 (OUT2A)
OUT3: LED7.2, LED7.3, MOTOR0.L, U$4.2 (OUT1A), U$4.3 (OUT1A), U$4.10 (OUT1B), U$4.11 (OUT1B)
OUT4: MOTOR0.R, R38.1, U$4.22 (OUT2B), U$4.23 (OUT2B), U$4.38 (OUT2A), U$4.39 (OUT2A)
RAW_SPWR: C27.1, R29.1, R36.2, SERVO_PWR.L, U$8.5 (D), U$8.6 (D), U$8.7 (D), U$8.8 (D), U$8.PAD (D), U$9.4 (G)
RESET: C30.2, IC3.14 (NRST), JP3.5, R7.1, RESET.1 (S), RESET.2 (S1)
SERVO0: IC3.59 (PD12), J16.8
SERVO1: IC3.60 (PD13), J16.7
SERVO2: IC3.61 (PD14), J16.6
SERVO3: IC3.62 (PD15), J16.5
SERVO4: IC3.63 (PC6), J16.4
SERVO5: IC3.64 (PC7), J16.3
SERVO6: IC3.65 (PC8), J16.2
SERVO7: IC3.66 (PC9), J16.1
SERVO_SENSE: IC3.34 (PC5), R40.2, R41.1
SPI1_MISO: IC3.31 (PA6), J5.4
SPI1_MOSI: IC3.32 (PA7), J5.3
SPI1_NSS: IC3.77 (PA15), J5.6
SPI1_SCK: IC3.30 (PA5), J5.5
SPI3_MISO: IC3.79 (PC11), SD.7 (DO)
SPI3_MOSI: IC3.80 (PC12), SD.3 (DI)
SPI3_NSS: IC3.83 (PD2), SD.2 (CS)
SPI3_SCK: IC3.78 (PC10), SD.5 (SCK)
SPWR: J15.1, J15.2, J15.3, J15.4, J15.5, J15.6, J15.7, J15.8, R40.1, U$8.1 (S), U$8.2 (S), U$8.3 (S), U$9.1 (S), U$9.2 (S), U$9.3 (S)
SWDCLK: IC3.76 (PA14), J7.2
SWDIO: IC3.72 (PA13), J7.1
USART1_RX: IC3.93 (PB7), J6.3
USART1_TX: IC3.92 (PB6), J6.2
USART2_RX: IC3.87 (PD6), J3.2
USART2_TX: IC3.86 (PD5), J3.1
USB_5V: C22.2, C24.2, IC3.68 (PA9), Q1.1 (D), Q1.2 (D), Q1.5 (D), Q1.6 (D), Q1.8 (D), USB2.VBUS
USB_DEV_DM: C14.1, IC3.70 (PA11), R46.2
USB_DEV_DP: C13.1, IC3.71 (PA12), R47.2
USB_HOST_DM: C18.1, IC3.53 (PB14), R49.2
USB_HOST_DP: C17.1, IC3.54 (PB15), R48.2
USB_HOST_EN: IC3.52 (PB13), U$2.4 (EN)
USB_HOST_FAULT: IC3.51 (PB12), U$2.5 (FAULT)

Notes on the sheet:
Aithon Board
Brian Gomberg, John Seng, Connor Citron

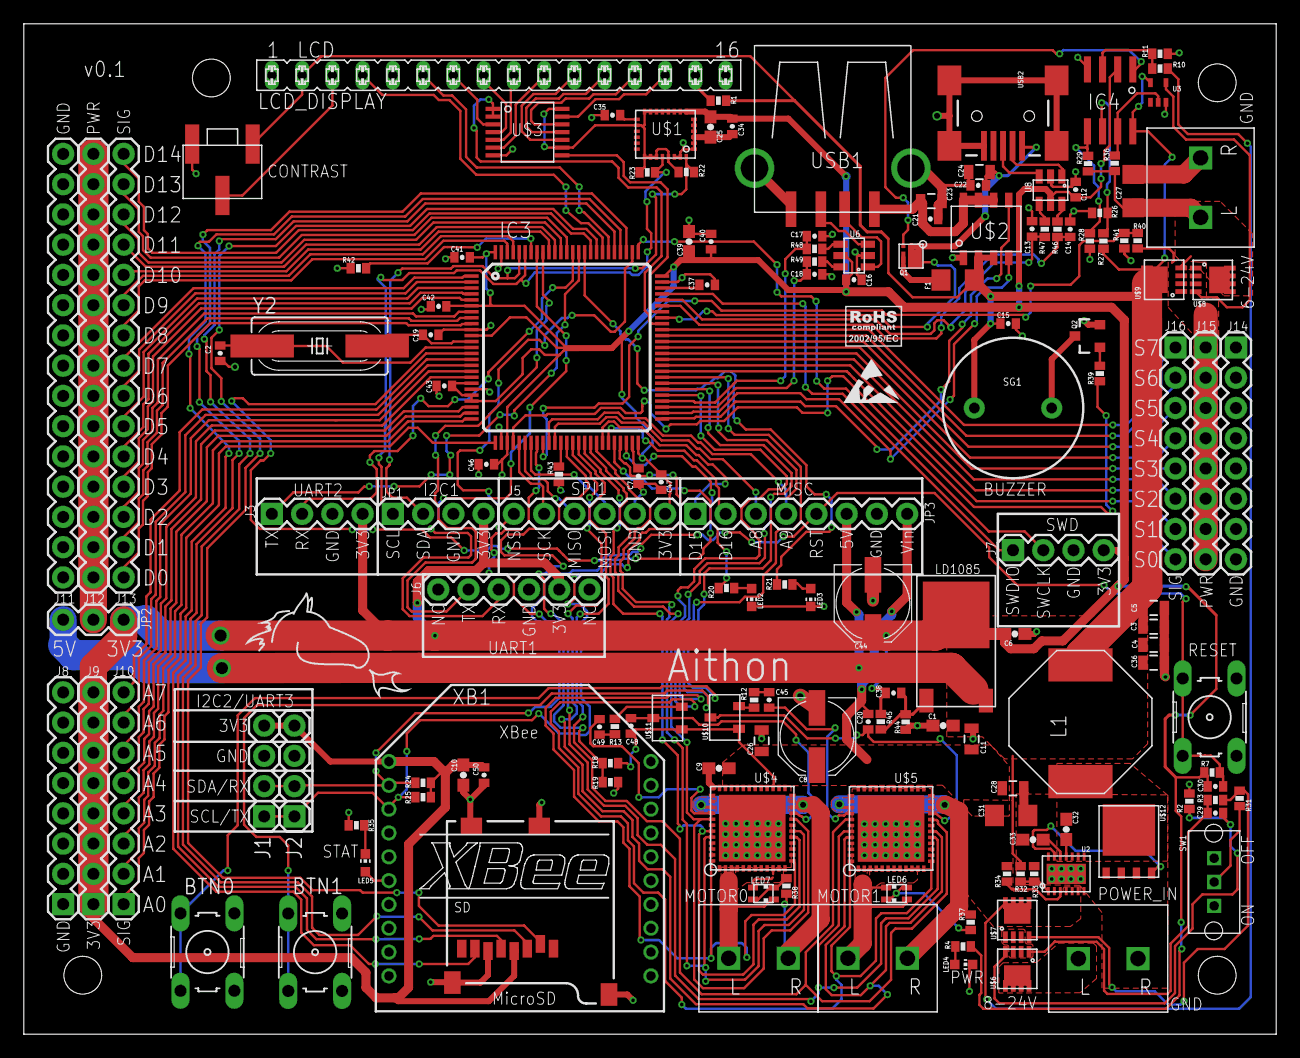
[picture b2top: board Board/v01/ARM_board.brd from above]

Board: 4 copper layers, 105.2 x 84.8 mm, 153 parts (0 on the bottom side), 153 nets.

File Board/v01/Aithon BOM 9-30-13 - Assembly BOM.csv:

Qty,Reference Designator,Description,Package,Part Number
3,"BTN1, BTN2, RESET",6x6x7mm tactile switch,4-PTH,
1,C9,CAP 0.1u 50V,0603,
12,"C12,C15,C16,C21,C22,C29,C34,C38,C40,C41,C42,C43",CAP 0.1u 50V,0402,
1,C8,CAP 100u,PANASONIC_D,
2,"C10, C32",CAP 1u 10V,0603,
1,C46,CAP 1u 10V,0402,
1,C11,CAP 0.1u,0805,
2,"C7, C37",CAP 2.2u 6.3V,0402,
4,"C1, C6, C25, C33",CAP 10u 10V,0603,
4,"C23, C24, C26, C28",CAP 10u 25V,0805,
1,C39,CAP 4.7u 6.3V,0603,
1,C50,CAP 8.2p,0402,
5,"C30, C35, C45, C47, C49",CAP 10n 50V,0402,
4,"C3, C4, C5, C36",CAP 22u 6.3V,0805,
2,"C27, C31",CAP 22u 25V,1206,
4,"C13, C14, C17, C18",CAP 47p 50V,0402,
1,C44,CAP ALUM 220u 16V,PANASONIC_D,
2,"C2, C19",CAP 20p,0402,
2,"C20, C48",CAP 0.22u,0402,
1,R1,RES 10 1/10W 5%,0402,
12,"R7,R10,R11,R19,R26,R28,R31,R36,R39,R41,R42,R43",RES 10k 1/10W 5%,0603,
4,"R46, R47, R48, R49",RES 15 1/10W 5%,0402,
1,R33,RES 18k 1/10W 5%,0402,
1,R45,RES 1.21k 1/10W 5%,0402,
2,"R27, R29",RES 39k 1/10W 5%,0402,
3,"R18, R32, R40",RES 93.1k 1/10W 1%,0402,
3,"R2, R3, R34",RES 100k 1/10W 5%,0402,
4,"R4, R20, R21, R35",RES 220 1/10W 5%,0402,
3,"R37, R38, R44",RES 2k 1/4W 5%,0402,
4,"R22, R23, R24, R25",RES 4.7k 1/10W 1%,0402,
2,"R12, R13",RES 100,0402,
1,POT,TRIMMER 10k 1/2W,3-SMD,3361S-1-103GLF
-,"J14,J15,J16","1x40 0.1"" male header",various PTH,
-,"J1,J2,J3,J5,J6,J7,J8,J9,J10,J11,J12,J13,JP1,JP2,JP3, LCD","1x40 0.1"" female header",various PTH,
1,L1,INDUCTOR - 2.7u 10A,2-SMD,VLF12060T-2R7N100
4,"MOTOR1, MOTOR2, POWER, SERVO_PWR",2 position screw terminal,2-PTH,
1,Y2,8MHz CRYSTALSMD HC49UP,2-SMD,
1,F1,PTC RESETABLE 1A,1206,
1,SW1,SW SLIDE 0.1A,3-PTH,
1,USB1,CONN USB R/A A TYPE,4-SMT + 2 PTH,1001-002-01100
1,USB2,CONN RCPT USB MINI B R/A,5-SMT + 4 tab,UX60SC-MB-5ST(80)
1,SD,CONN MINI MICRO-SD 8PIN,8-SMD,101-00581-59
2,XB1,10pin 2mm female header,10-PTH,
1,LED4,LED RED,0603,
3,"LED2, LED3, LED5",LED YELLOW,0603,
2,"LED6, LED7",LED R/G,0606,
1,SG1,BUZZER,2-PTH,
1,LD1085,AP1084,DPAK,
1,U$3,8BIT SHIFT REGISTER,14-TSSOP,MC74HC164
4,"U$6, U$7, U$8, U$9",SI7617,POWERPAK1212-8,SI7617
2,"U$10, U$11",BAV99,SOT-23,
1,U2,REG BUCK ADJ 10A,14-WDFN,RT7259
1,U3,INVERTER,6-TSSOP (5-lead),NC7SZU04
1,LCD,16x2 character LCD screen,NOT PLACED,external board
2,"U$4, U$5",Motor Driver,VFQFPN48,L6206Q
1,Q1,P-MOSFET 4A,POWERFLAT2x2,STL4P2UH7
1,Q2,NPN Transistor,SOT23-3,2STR1230
1,U$12,P-MOSFET 19A,POWERFLAT5x6,STL85N6F3
2,"U6, U8",ESD PROTECTION,SOT23-6L,USBLC6-2
1,IC3,STM32F4 MCU 32BIT,100-LQFP,STM32F437VI
1,U$2,PWR SW USB 1A,SO-8,STMPS2171MTR
1,IC4,DUAL OP AMP,8-SOIC,LM358DT
1,U$1,ACCEL/GYRO,28-TFLGA,LSM330DLC

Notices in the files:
parts and their libraries:
SparkFun-Resistors: Licensing: CC v3.0 Share-Alike You are welcome to use this library for commercial purposes.
